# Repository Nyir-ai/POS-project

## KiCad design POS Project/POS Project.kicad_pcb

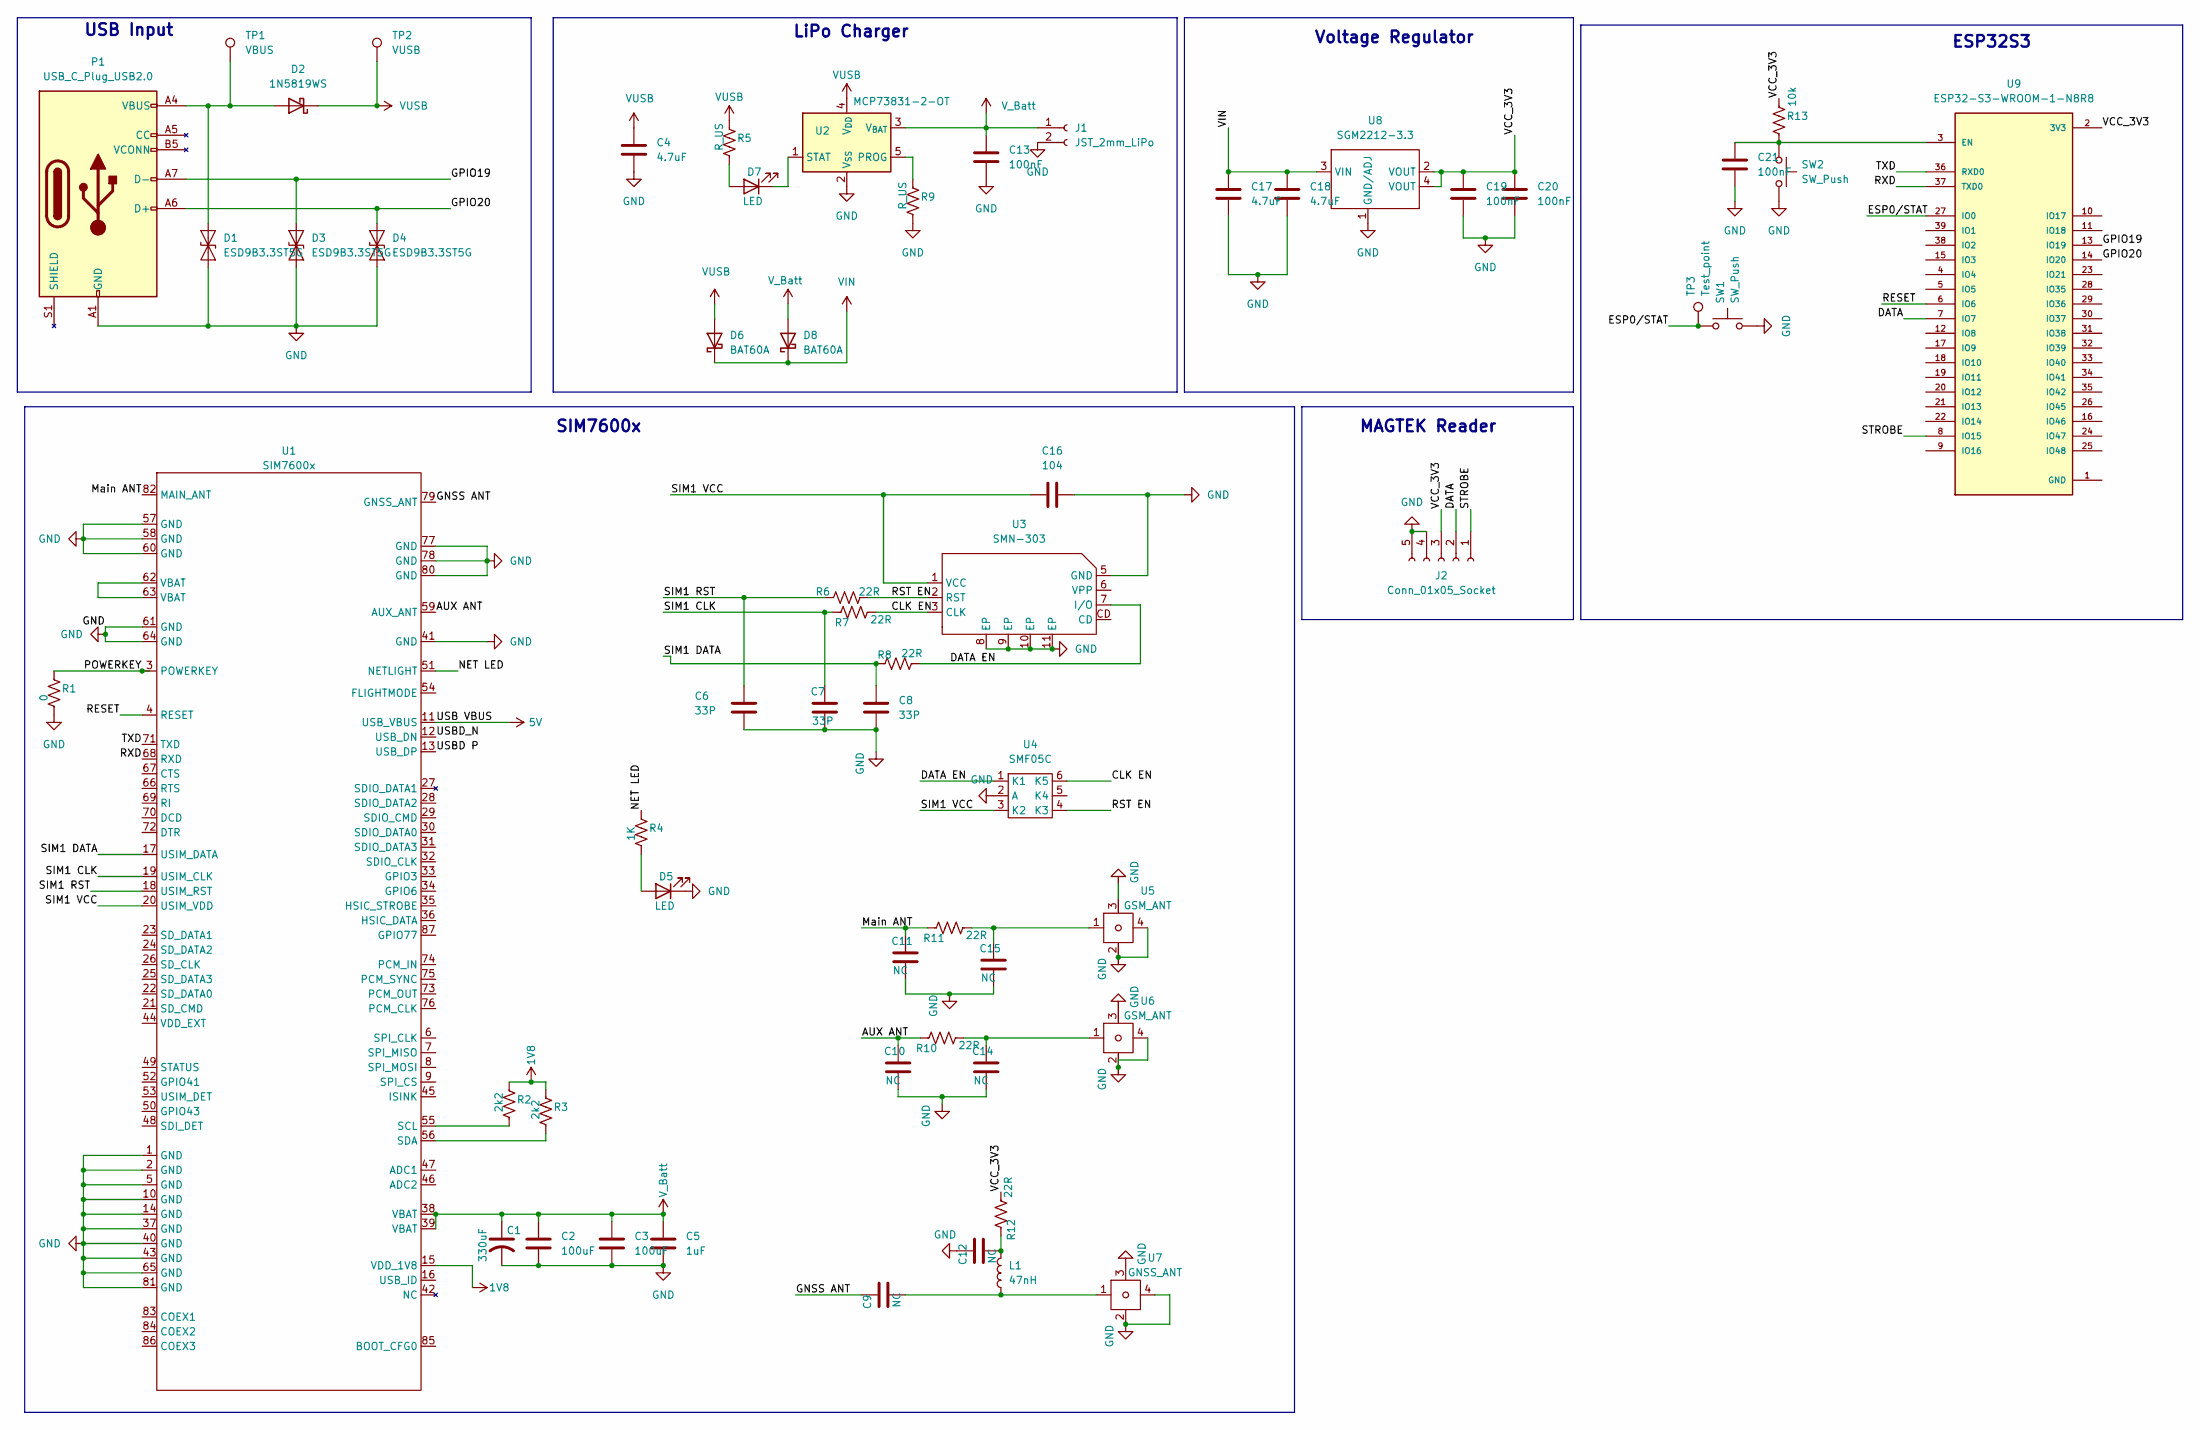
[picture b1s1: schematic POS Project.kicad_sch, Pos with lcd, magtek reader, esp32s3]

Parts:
C1: 330uF; CP_Elec_10x12.5
C2, C3: 100uF; C_0805_2012Metric
C4, C17, C18: 4.7uF; C_0805_2012Metric
C5: 1uF; C_0805_2012Metric
C6, C7, C8: 33P; C_0805_2012Metric
C9, C10, C11, C12, C14, C15: NC; C_0805_2012Metric
C13, C19, C20, C21: 100nF; C_0805_2012Metric
C16: 104; C_0805_2012Metric
D1, D3, D4: ESD9B3.3ST5G; D_SOD-923
D2: 1N5819WS; D_SOD-323
D5, D7: LED; LED_0805_2012Metric
D6, D8: BAT60A; D_SOD-323
J1: JST_2mm_LiPo; TE_440054-2_1x02_P2.00mm_Vertical
J2: Conn_01x05_Socket; Molex_PicoBlade_53047-0510_1x05_P1.25mm_Vertical
L1: 47nH; L_0805_2012Metric
P1: USB_C_Plug_USB2.0; USB_C_Receptacle_GCT_USB4105-xx-A_16P_TopMnt_Horizontal
R1: 0; R_0805_2012Metric
R2, R3: 2k2; R_0805_2012Metric
R4: 1K; R_0805_2012Metric
R5, R9: R_US; R_0805_2012Metric
R6, R7, R8, R10, R11, R12: 22R; R_0805_2012Metric
R13: 10k; R_0805_2012Metric
SW1, SW2: SW_Push; SW_PUSH_6mm
TP1: VBUS; TestPoint_Pad_1.0x1.0mm
TP2: VUSB; TestPoint_Pad_1.0x1.0mm
TP3: Test_point; TestPoint_Pad_1.0x1.0mm
U1: SIM7600x; IC_SIM7600G
U2: MCP73831-2-OT; SOT-23-5
U3: SMN-303; SIM-SMD_SMN-303
U4: SMF05C; SOT-363_SC-70-6
U5, U6: GSM_ANT; U.FL_Molex_MCRF_73412-0110_Vertical
U7: GNSS_ANT; U.FL_Molex_MCRF_73412-0110_Vertical
U8: SGM2212-3.3; SOT-223
U9: ESP32-S3-WROOM-1-N8R8; XCVR_ESP32S3WROOM1N8R8

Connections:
1V8: R2.1, R3.1, U1.15 (VDD_1V8)
5V: U1.11 (USB_VBUS)
/AUX ANT: C10.2, R10.1, U1.59 (AUX_ANT)
/CLK EN: R7.2, U3.3 (CLK), U4.6 (K5)
/DATA: J2.2 (DATA), U9.7 (IO7)
/DATA EN: R8.2, U3.7 (I/O), U4.1 (K1)
/ESP0/STAT: SW1.1, TP3.1, U9.27 (IO0)
/GNSS ANT: C9.2, U1.79 (GNSS_ANT)
/GPIO19: D3.2 (A2), P1.A7 (D-), U9.13 (IO19)
/GPIO20: D4.2 (A2), P1.A6 (D+), U9.14 (IO20)
/Main ANT: C11.2, R11.1, U1.82 (MAIN_ANT)
/NET LED: R4.1, U1.51 (NETLIGHT)
/POWERKEY: R1.1, U1.3 (POWERKEY)
/RESET: U1.4 (RESET), U9.6 (IO6)
/RST EN: R6.2, U3.2 (RST), U4.4 (K3)
/RXD: U1.68 (RXD), U9.37 (TXD0)
/SIM1 CLK: C7.2, R7.1, U1.19 (USIM_CLK)
/SIM1 DATA: C8.2, R8.1, U1.17 (USIM_DATA)
/SIM1 RST: C6.2, R6.1, U1.18 (USIM_RST)
/SIM1 VCC: C16.1, U1.20 (USIM_VDD), U3.1 (VCC), U4.3 (K2)
/STROBE: J2.1 (STROBE), U9.8 (IO15)
/TXD: U1.71 (TXD), U9.36 (RXD0)
/USBD P: U1.13 (USB_DP)
/USBD_N: U1.12 (USB_DN)
/VCC_3V3: C19.1, C20.1, J2.3 (VDD), R12.2, R13.1, U8.2 (VOUT), U8.4 (VOUT), U9.2 (3V3)
unnamed: C9.1, L1.1, U7.1
unnamed: C12.1, L1.2, R12.1
unnamed: C14.2, R10.2, U6.1
unnamed: C15.2, R11.2, U5.1
unnamed: D1.2 (A2), D2.2 (A), P1.A4 (VBUS), P1.A9 (VBUS), P1.B4 (VBUS), P1.B9 (VBUS), TP1.1
unnamed: D5.2 (A), R4.2
unnamed: D7.2 (A), R5.2
unnamed: D7.1 (K), U2.1 (STAT)
unnamed: R2.2, U1.55 (SCL)
unnamed: R3.2, U1.56 (SDA)
unnamed: U1.62 (VBAT), U1.63 (VBAT)
unnamed: R9.1, U2.5 (PROG)
unnamed: C21.1, R13.2, SW2.1, U9.3 (EN)
VIN: C17.1, C18.1, D6.1 (K), D8.1 (K), U8.3 (VIN)
VUSB: C4.1, D2.1 (K), D6.2 (A), R5.1, TP2.1, U2.4 (V_{DD})
V_Batt: C1.1, C2.1, C3.1, C5.1, C13.1, D8.2 (A), J1.1, U1.38 (VBAT), U1.39 (VBAT), U2.3 (V_{BAT})

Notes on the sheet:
LiPo Charger
Voltage Regulator
ESP32S3
MAGTEK Reader
SIM7600x
USB Input

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
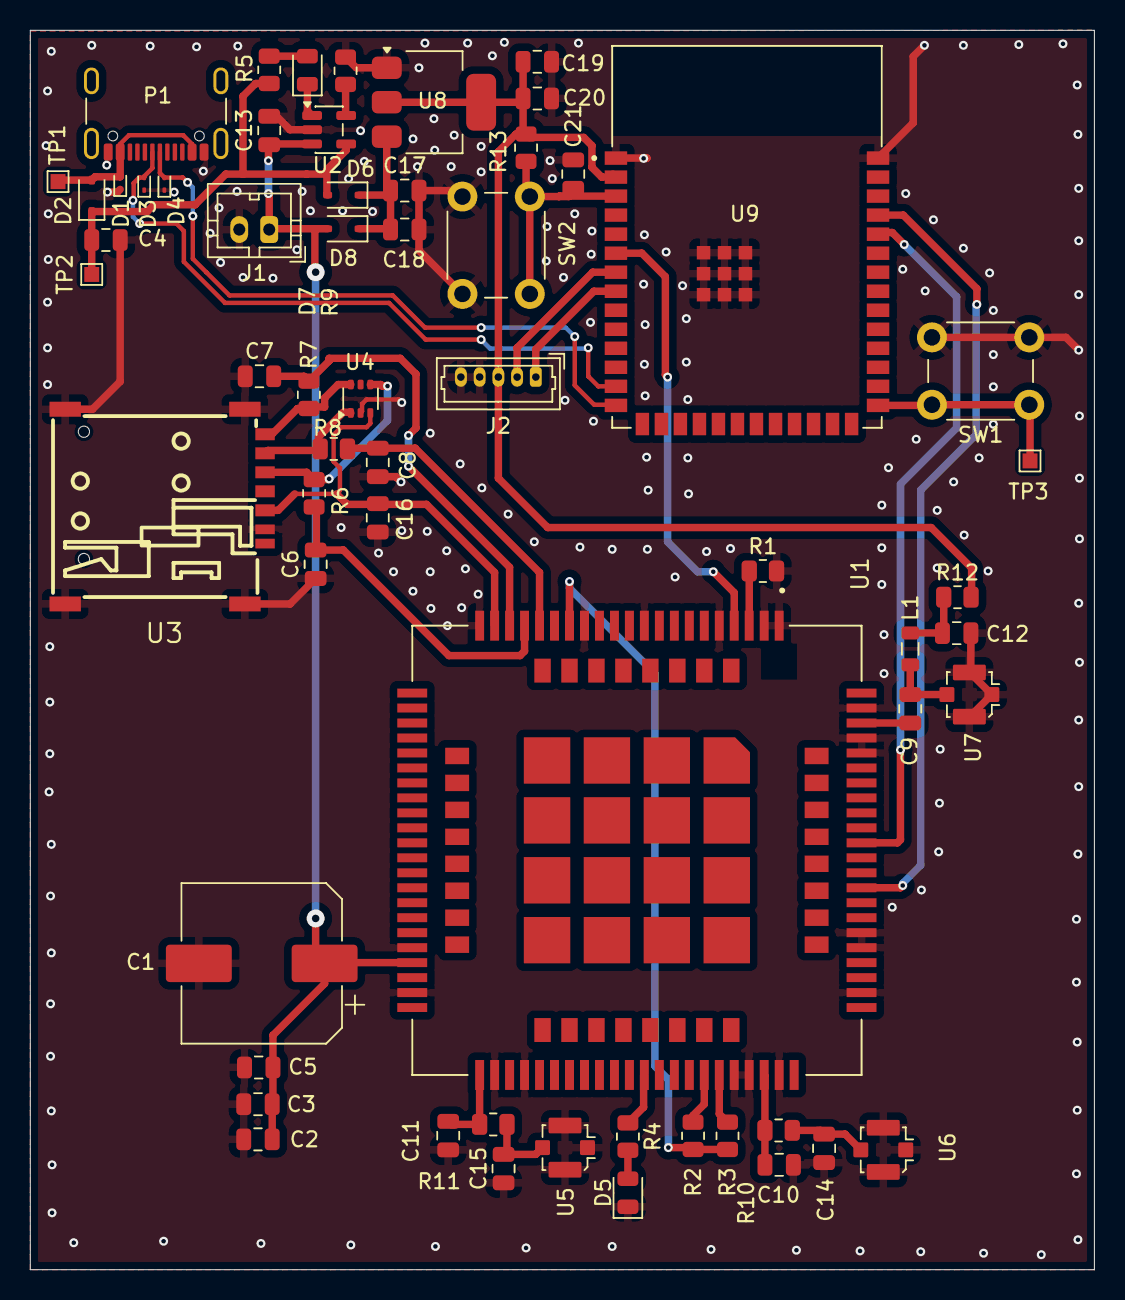
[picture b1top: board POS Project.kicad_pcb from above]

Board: 2 copper layers, 71.0 x 82.8 mm, 60 parts (0 on the bottom side), 39 nets.

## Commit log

2025-12-26 added power circuit
2026-01-11 added sim7600 symbol
2026-01-15 modified sim7600x symbol
2026-01-16 updated SIM7600x scematic
2026-01-16 added sim card and tvs1 schematic
2026-01-22 added esp32s3
2026-01-23 added esp32s3, voltage reg, magtek schematic
2026-01-29 Added footprints for some of the components
2026-02-06 added PCB board
2026-02-12 organized PCB components
2026-02-13 added PCB routs
2026-02-19 made final changes to pcb
2026-02-20 created fabrication files
